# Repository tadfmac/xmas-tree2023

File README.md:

# xmas-tree2023

Xmas Tree基板

## 基板作成方法

[JLCPCB用 gerberデータ](https://github.com/tadfmac/xmas-tree2023/tree/main/gerber/forJLCPCB/v0.2) を https://jlcpcb.com へ 2Layer で頼めば届きます。

## 部品一覧

|パーツ|数量|
|:---|---:|
|[Seeed XIAO RP2040](https://www.seeedstudio.com/XIAO-RP2040-v1-0-p-5026.html)|1|
|WS2812B (v5でない旧ver.)|15|
|[PL9823-F5](https://akizukidenshi.com/catalog/g/gI-08411/)|1|
|500mA ポリスイッチ (1206)|1|
|抵抗 10kΩ (0603)|3|
|コンデンサ 10uF (0805)|16|
|スライドスイッチ (MSS22D18-SMD)|1|
|M3ナベネジ 20mm|1|
|M3ナット|1|

上記に加えて USB-Cケーブル（推奨：USB-C側がL字のもの）が必要です。（PC側のコネクタ形状はPCの仕様による）

## ファームウエア

- [test (LED blinkのみ)](./arduino/test/test.ino)
- [usb-midi (WIP)](./arduino/usb-midi/usb-midi.ino)

## usb-midi ver.のテスト

```
cd xmas-tree2023
npm i
node ./app.mjs
```
これで webサーバが立ち上がるので、ブラウザから下記URLにアクセス

```
http://localhost:2000/
```
画面には何も表示されませんが、xmas-tree2023を接続するとLEDが点滅します。

## スタンド (3Dデータ)

[ファイル](./3dprint/stand/TreeStand1.stl)

## Licenses

MIT

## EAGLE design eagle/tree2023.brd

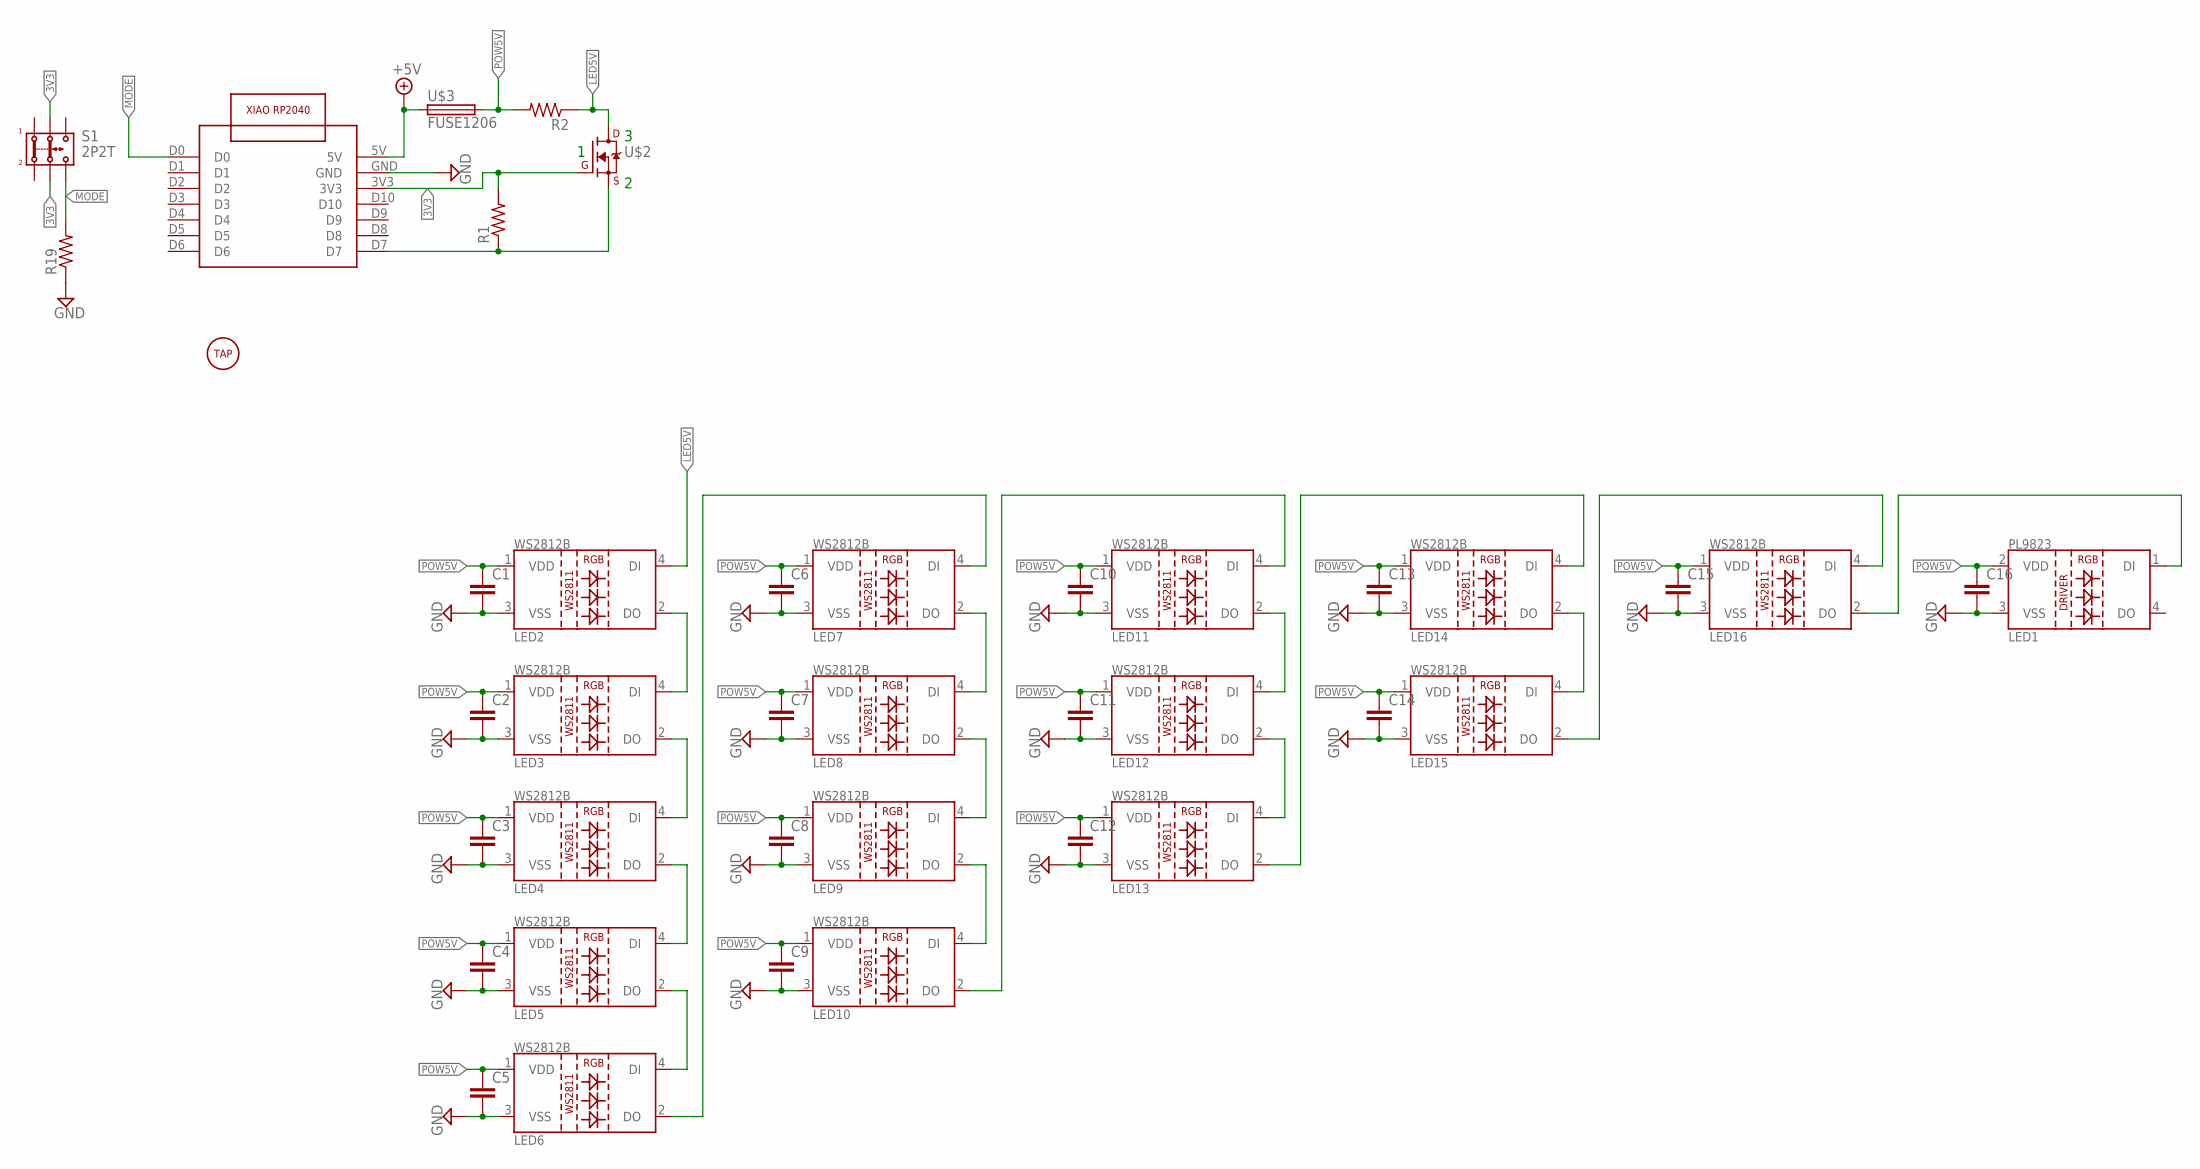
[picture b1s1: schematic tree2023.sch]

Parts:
C1, C2, C3, C4, C5, C6, C7, C8, C9, C10, C11, C12, C13, C14, C15, C16: C-EUC0805; C0805
LED1: LED-PL9823-F5
LED2, LED3, LED4, LED5, LED6, LED7, LED8, LED9, LED10, LED11, LED12, LED13, LED14, LED15, LED16: LED-WS2812B
R1, R2, R19: R-US_R0603; R0603
S1: 2P2T
U$1: XIAO-RP2040FRONT-SMD; XIAO-RP2040-ASIDE-SMD
U$2: IRML6344; SOT23
U$3: FUSE1206; F1206
U$4: TAPHOLE3MM; TAPHOLE-3MM

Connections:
3V3: R1.2, S1.2.1, S1.2.2, U$1.3V3, U$2.1 (G)
+5V: U$1.5V, U$3.1
GND: C1.2, C2.2, C3.2, C4.2, C5.2, C6.2, C7.2, C8.2, C9.2, C10.2, C11.2, C12.2, C13.2, C14.2, C15.2, C16.2, LED1.3 (VSS), LED2.3 (VSS), LED3.3 (VSS), LED4.3 (VSS), LED5.3 (VSS), LED6.3 (VSS), LED7.3 (VSS), LED8.3 (VSS), LED9.3 (VSS), LED10.3 (VSS), LED11.3 (VSS), LED12.3 (VSS), LED13.3 (VSS), LED14.3 (VSS), LED15.3 (VSS), LED16.3 (VSS), R19.1, U$1.GND
LED5V: LED2.4 (DI), R2.1, U$2.3 (D)
MODE: R19.2, S1.3.2, U$1.D0
unnamed: LED2.2 (DO), LED3.4 (DI)
unnamed: LED3.2 (DO), LED4.4 (DI)
unnamed: LED4.2 (DO), LED5.4 (DI)
unnamed: LED5.2 (DO), LED6.4 (DI)
unnamed: LED6.2 (DO), LED7.4 (DI)
unnamed: LED7.2 (DO), LED8.4 (DI)
unnamed: LED8.2 (DO), LED9.4 (DI)
unnamed: LED9.2 (DO), LED10.4 (DI)
unnamed: LED10.2 (DO), LED11.4 (DI)
unnamed: LED11.2 (DO), LED12.4 (DI)
unnamed: LED12.2 (DO), LED13.4 (DI)
unnamed: LED13.2 (DO), LED14.4 (DI)
unnamed: LED14.2 (DO), LED15.4 (DI)
unnamed: LED15.2 (DO), LED16.4 (DI)
unnamed: LED1.1 (DI), LED16.2 (DO)
unnamed: R1.1, U$1.D7, U$2.2 (S)
POW5V: C1.1, C2.1, C3.1, C4.1, C5.1, C6.1, C7.1, C8.1, C9.1, C10.1, C11.1, C12.1, C13.1, C14.1, C15.1, C16.1, LED1.2 (VDD), LED2.1 (VDD), LED3.1 (VDD), LED4.1 (VDD), LED5.1 (VDD), LED6.1 (VDD), LED7.1 (VDD), LED8.1 (VDD), LED9.1 (VDD), LED10.1 (VDD), LED11.1 (VDD), LED12.1 (VDD), LED13.1 (VDD), LED14.1 (VDD), LED15.1 (VDD), LED16.1 (VDD), R2.2, U$3.2

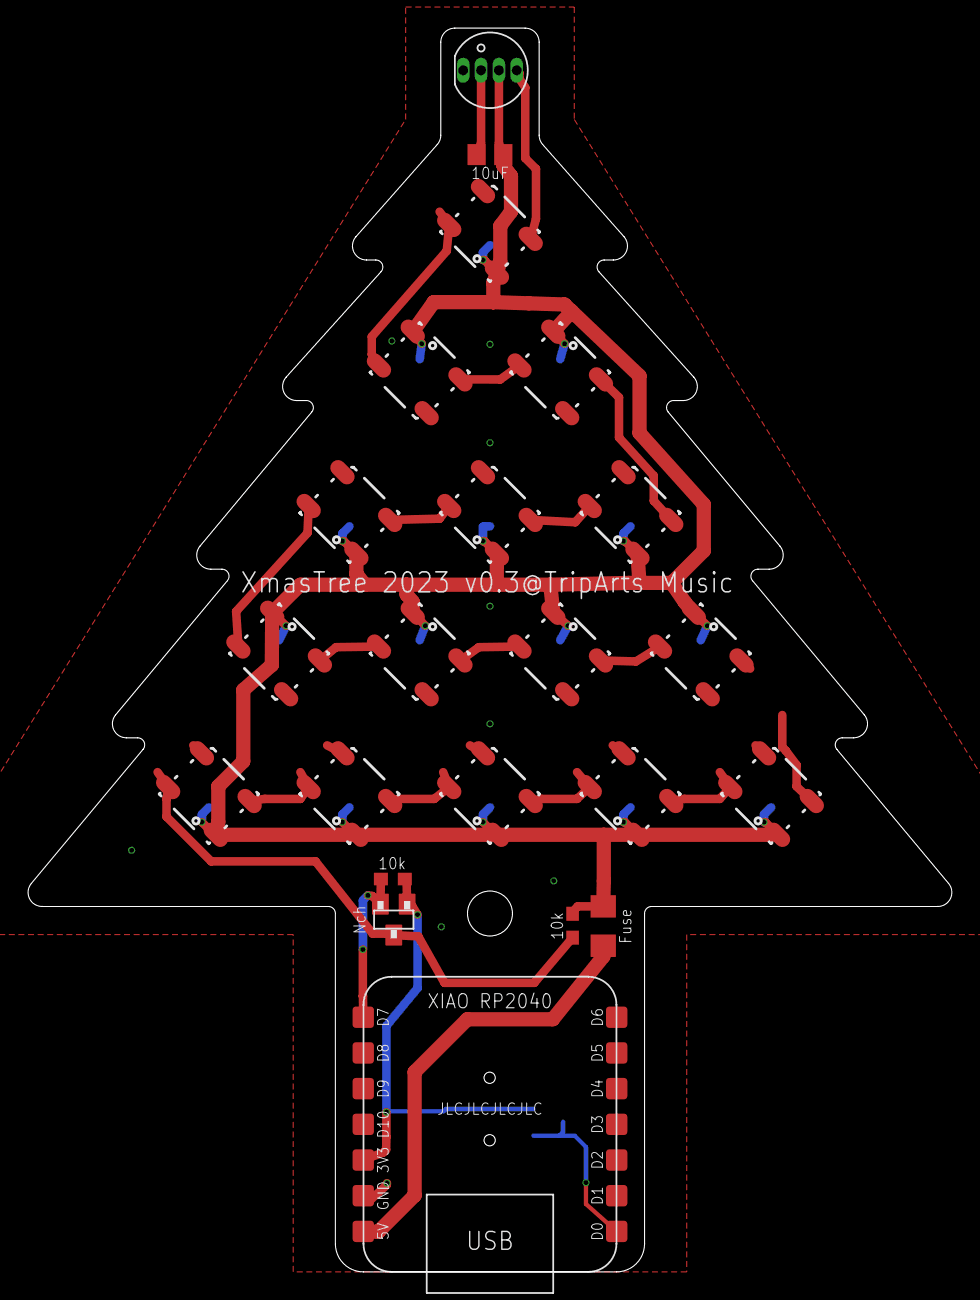
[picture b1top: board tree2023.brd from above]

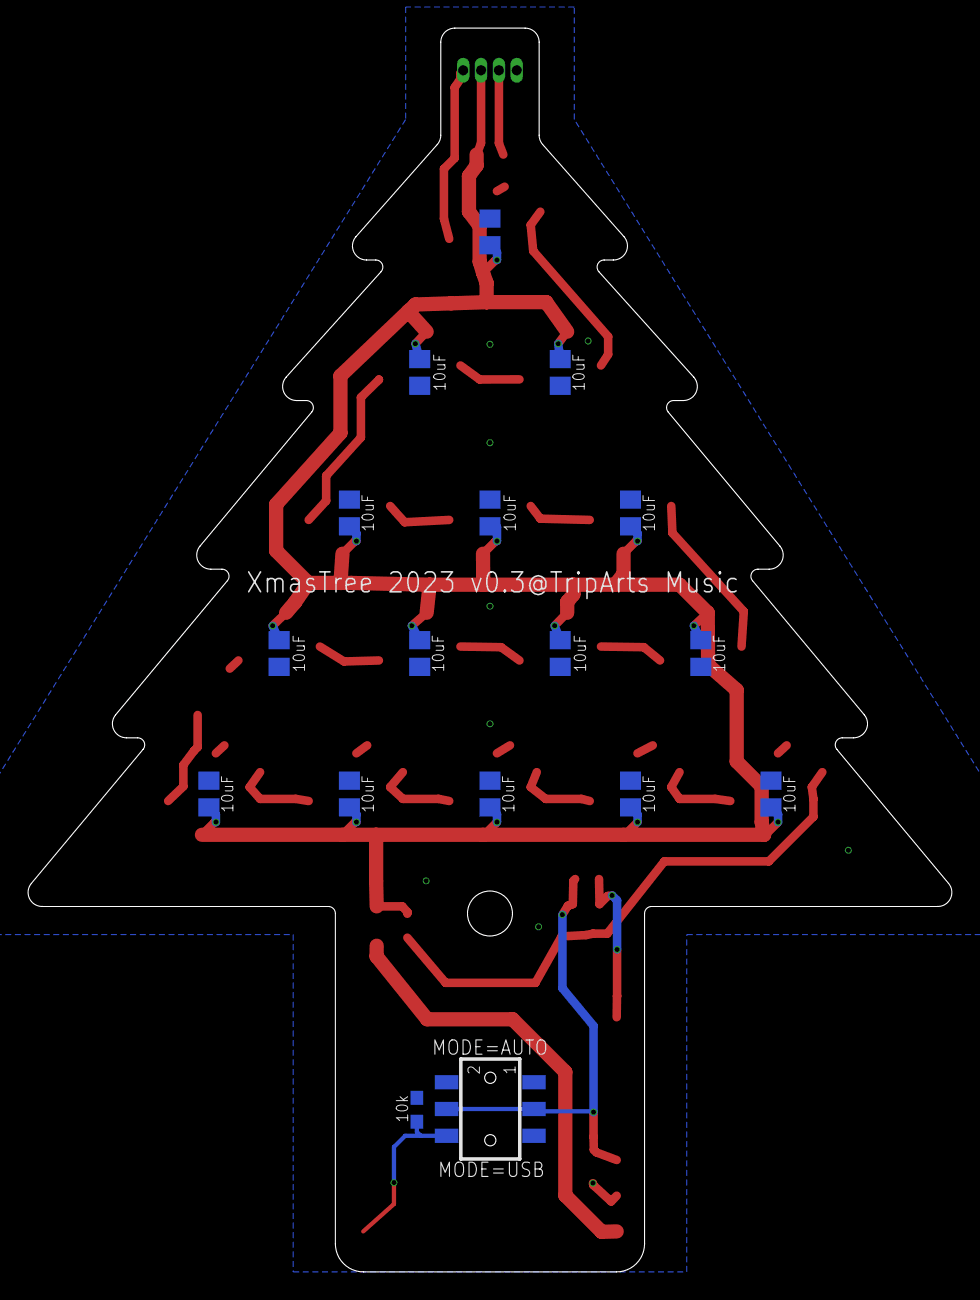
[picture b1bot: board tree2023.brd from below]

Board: 2 copper layers, 65.7 x 88.5 mm, 40 parts (17 on the bottom side), 22 nets.

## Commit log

2023-12-22 add pcb files
2023-12-22 add image
2023-12-22 add parts list
2023-12-23 pcb files update
2023-12-23 add test firmware
2023-12-23 add stand stl file
2023-12-23 update test firmware
2024-10-11 add test html
2024-10-15 fix uuid generator
2024-10-15 fix example
2024-10-24 fix top color and examples
